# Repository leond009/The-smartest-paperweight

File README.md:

# The-smartest-paperweight

Hi there! Im happy to present you the smartest paperweight ever!

As the name suggests, the project is a hockey puck sized thing(?) that you can interact with it. Essentially, it features many sensors to detect what is going on around it and reacts accordingly to each change (Specifically, to temperature, humidity, light and motion). This project is meant to be kept as a small companion on your desk and keep you company through its OLED screen and RBG led. The idea came to me after seeing the MESS i had in my desk and realizing that even inanimate object that don't really serve a purpose can also bee companions, and i took that idea to the next level.

Here is a thourough description of what each component does:

Sensors and Internal components that the user does not interact with:
~ It features the MPU6050 Gyroscope and accelerometer to detect movement of the project and have the reactive components react accordingly to the movement. It is also planned that in order to check information of the weather, humidity and temperatre, the user moves the paperweight with a certain gesture.
~ It features a Photoresistor paired with a 10kohm resistor to react to sorrounding light. I included this to make sure the paperweight didnt become to distrative at night and also possibly include it in weather reaction.
~ It fetures the DHT11 sensor to detect humidity and temperature. Because of this sensor it is very important that the case is not fully enclosed, otherwise the measurements become not onlz inaccurate but one of tha main purposes of the Paperweight (Ambient reaction) is rendered useless.
~ To power the whole project, I plan to use a 100mAh(This can eventually be changed to a battery with larger capacity) Lipo battery paired with the TP4056 to charge the battery.
~In order to prevent any damage caused by power fluctuations as some of the components are directly powered through the battery, i included the AMS1117 for power regulation.
~The whole system is controlled with an ESP32, eventually, through Bluetooth the user can change the color of the paperweight according to what the PW is sensing.

Components that the user interacts with:
~The project features and 1.13 inch OLED controlled with I2C to save up on GPIO pins. On the display two robot eyes are displayed and they react to the environment according to what the sensors are measuring. Moreover, using the gestures measured with the MPU6050, the user can check the power left on the battery
~The project also features an RBG led paired with 330 OHM resistors to change the color of the paperweight. (Nothe that this means that the enclosure MUST be translusent or transparent)
~Thanks to the TPU4056 the user can charge the battery using a simple microUSB cable.

Here are some pictures of the project!

PARTS LIST of the funding list
| [Esp32-S3-N16R8](https://www.electronicadiy.com/products/placa-de-desarrollo-wifi-bluetooth-esp32-s3-n16r8?variant=48511995019522) | Microcontroller of the project | 1 | $15.32 | $15.32 | [Electronica DIY](https://www.electronicadiy.com/products/placa-de-desarrollo-wifi-bluetooth-esp32-s3-n16r8?variant=48511995019522) |
| --- | --- | --- | --- | --- | --- |
| [Oled screen 1.3" SH1106 I2C](https://www.electronicadiy.com/products/pantalla-oled-1-3-sh1106?variant=43320054612226) | Screen to display the eyes of the PW | 1 | $11.26 | $11.26 | [Electronica DIY](https://www.electronicadiy.com/products/pantalla-oled-1-3-sh1106?variant=43320054612226) |

OTHER PARTS (that i already had lol)
| [TP4056](https://www.electronicadiy.com/products/modulo-de-carga-tp4056-con-proteccion) | Charging | 1 | $1.00 | $1.00 | [Electronica DIY](https://www.electronicadiy.com/products/modulo-de-carga-tp4056-con-proteccion) |
| --- | --- | --- | --- | --- | --- |
| [AMS1117](https://www.electronicadiy.com/products/convertidor-de-voltaje-5v-a-3-3v-ams1117?_pos=2&_sid=f3598c96b&_ss=r) | Power regulation| 1 | $0.50 | $0.50 | [Electronica DIY](https://www.electronicadiy.com/products/convertidor-de-voltaje-5v-a-3-3v-ams1117?_pos=2&_sid=f3598c96b&_ss=r) |
| [DHT111](https://www.electronicadiy.com/products/sensor-de-temperatura-y-humedad-dht11-ky-015?_pos=1&_sid=ee95e7ec1&_ss=r) | Temperature and Humidity sensor| 1 | $3.00 | $3.00 | [Electronica DIY](https://www.electronicadiy.com/products/sensor-de-temperatura-y-humedad-dht11-ky-015?_pos=1&_sid=ee95e7ec1&_ss=r) |
Resistors and minor extra components are not disclosed, everyone has one laying around haha

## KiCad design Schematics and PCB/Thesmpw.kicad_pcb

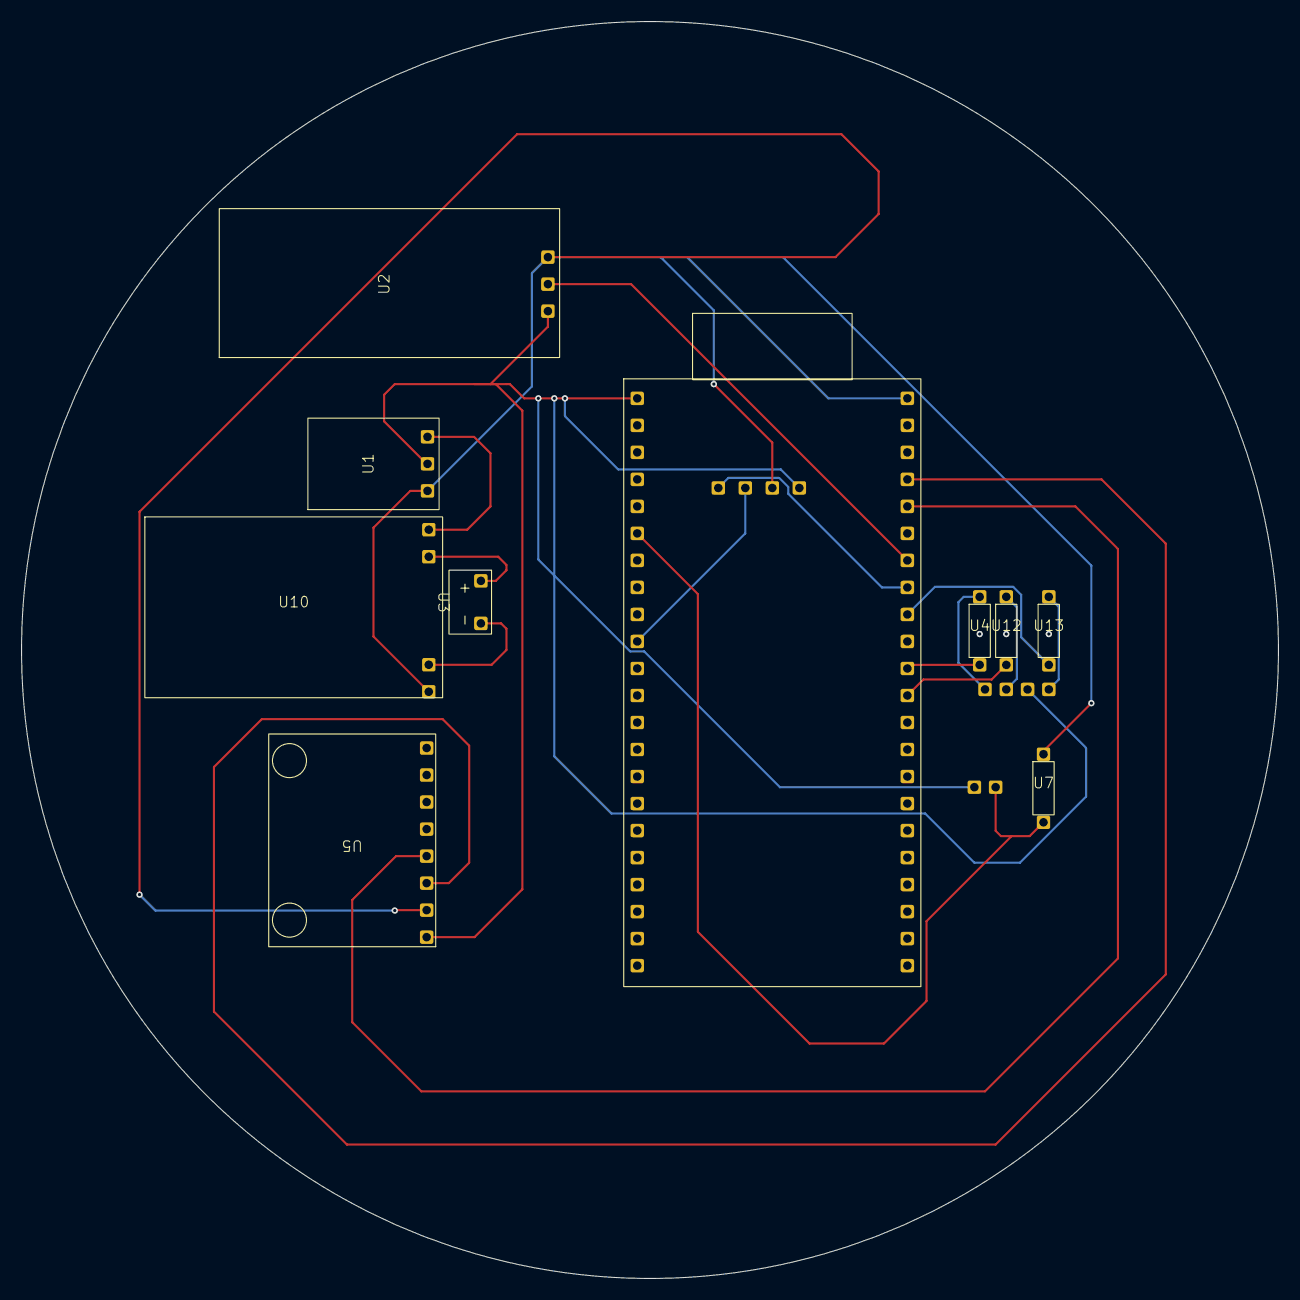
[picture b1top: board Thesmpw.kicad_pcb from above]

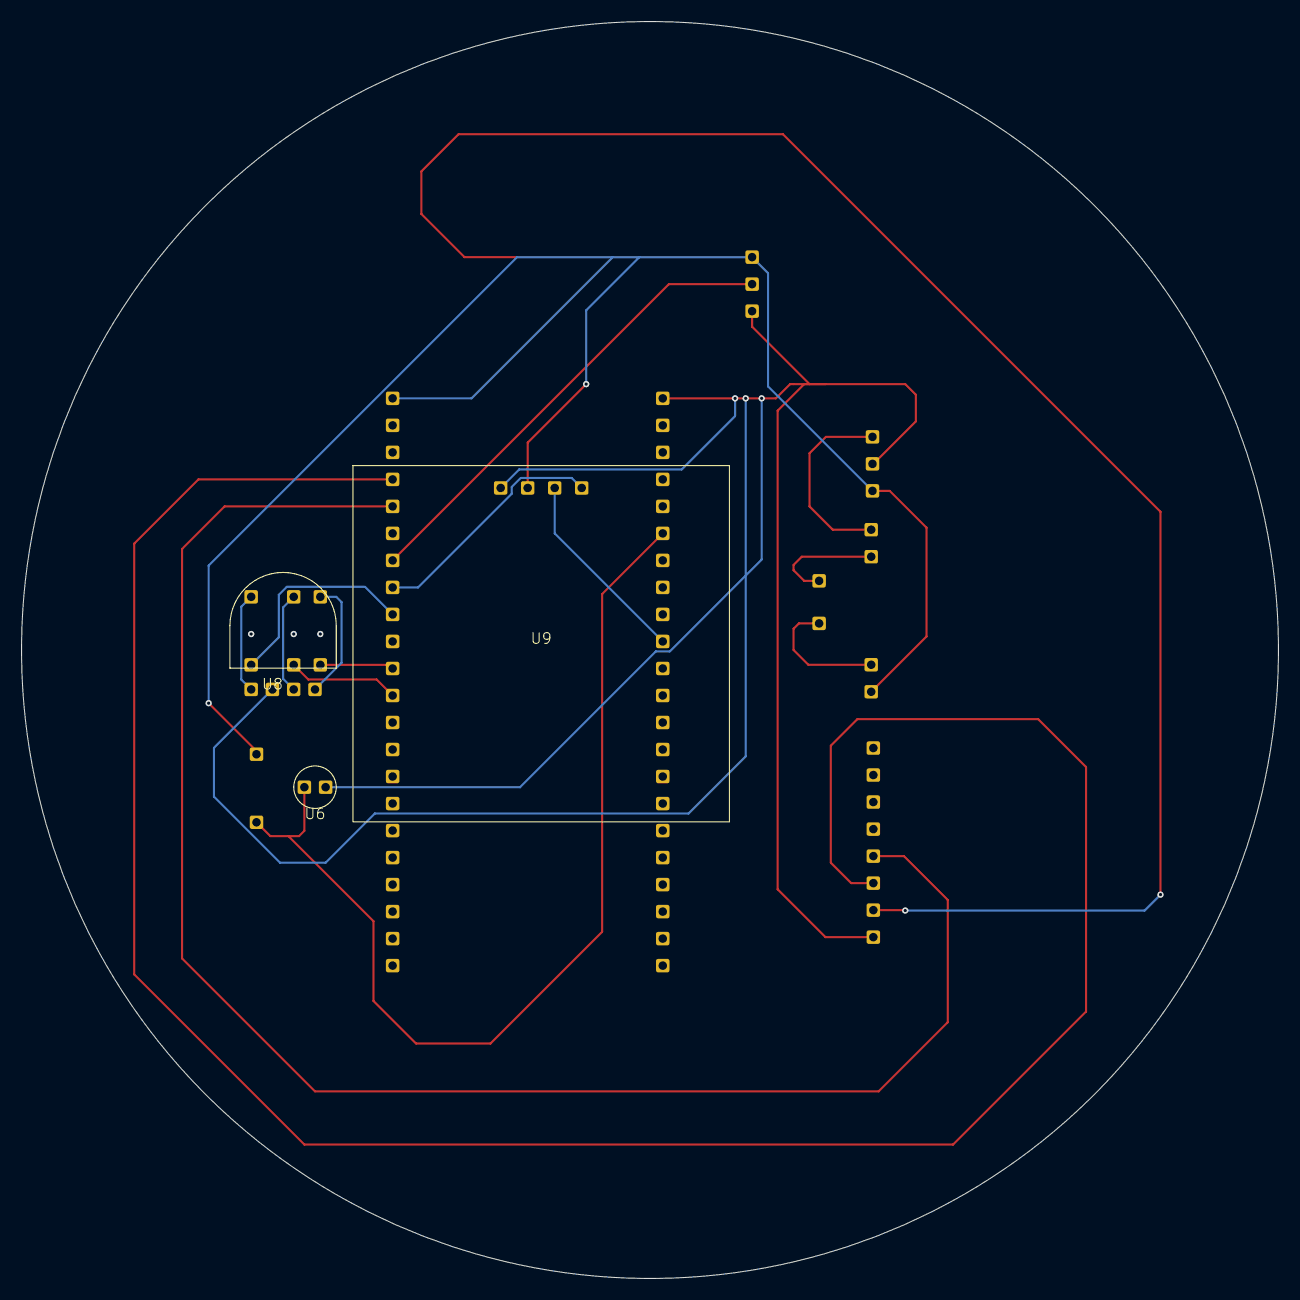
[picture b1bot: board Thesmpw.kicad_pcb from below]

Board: 2 copper layers, 118.2 x 118.2 mm, 13 parts (3 on the bottom side), 17 nets.

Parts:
U1: AMS1117
U2: DHT11
U3: Battery
U4, U7, U12, U13: RESISTOR
U5: MPU-6050
U6: PHOTORESISTOR
U8: RGB LEd
U9: 1.3 inch Oled
U10: TPU4056
U11: ESP32_OFICIAL

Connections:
unnamed: U1.1 (GND), U2.3 (-), U5.2 (GND), U7.1 (IN), U9.2 (VCC), U10.4 (OUT-), U11.23 (GND)
unnamed: U1.3 (INPUT), U10.1 (OUT+)
unnamed: U1.2 (OUTPUT), U2.1 (+), U5.1 (VCC), U6.1 (IN), U8.2 (+), U9.1 (GND), U11.1 (3V3)
unnamed: U4.1 (IN), U8.4 (B)
unnamed: U3.2 (+), U10.2 (B+)
unnamed: U3.1 (-), U10.3 (B-)
unnamed: U5.3 (SCL), U11.26 (GPIO1)
unnamed: U5.4 (SDA), U11.27 (GPIO2)
unnamed: U6.2 (OUT), U7.2 (OUT), U11.6 (GPIO6)
unnamed: U9.3 (SCL), U11.10 (GPIO17)
unnamed: U11.34 (GPIO36), U12.2 (OUT)
unnamed: U4.2 (OUT), U11.33 (GPIO37)
unnamed: U11.31 (GPIO39), U13.2 (OUT)
unnamed: U9.4 (SDA), U11.30 (GPIO40)
unnamed: U2.2 (OUT), U11.29 (GPIO41)
unnamed: U8.3 (G), U12.1 (IN)
unnamed: U8.1 (R), U13.1 (IN)
